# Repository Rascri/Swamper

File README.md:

# Swaby

## Descripción

**Swaby** es un proyecto investigativo orientado al desarrollo de un sistema portátil de monitoreo biomédico. El prototipo permite adquirir y visualizar en tiempo real información relacionada con la actividad cardíaca y el movimiento del usuario.

El sistema utiliza un **ESP32** como unidad principal de procesamiento, conectado a un sensor **AD8232** para la adquisición del electrocardiograma (ECG), un **DS18B20** para la medición de temperatura y un **MPU-6050** para el análisis de movimiento y postura.

Los datos obtenidos son procesados por el ESP32 y enviados mediante **Bluetooth** a una PC para su visualización y registro.

## Enfoque investigativo

El desarrollo de Swaby se planteó como un proyecto investigativo, además de la construcción de un prototipo funcional. Durante las pruebas se analizaron las condiciones necesarias para obtener una señal de ECG estable y las limitaciones del sistema.

Se comprobó que el ECG funciona correctamente cuando el usuario se encuentra en reposo, pero presenta importantes perturbaciones durante el movimiento. El principal problema identificado fue el ruido generado por la actividad y el movimiento muscular, que se superpone a la señal cardíaca y genera artefactos que dificultan su correcta interpretación.

A pesar del filtrado incorporado en el AD8232, filtrado por software y los recursos disponibles para el proyecto no fue posible eliminar estas interferencias de manera suficiente como para obtener una señal de ECG confiable durante el movimiento. Por este motivo, el monitoreo cardíaco se consideró funcional bajo condiciones de reposo, pero limitado durante la actividad física.

También se detectaron interferencias externas durante las primeras pruebas, relacionadas con la alimentación y la calidad de los electrodos. Estas fueron reducidas mediante el aislamiento de la fuente de alimentación utilizada en el laboratorio y el reemplazo de los electrodos por otros de mayor calidad.

## Software

El **ESP32** se encarga de adquirir los datos de los sensores y transmitirlos mediante Bluetooth.

Para la visualización y registro de los datos se desarrolló una aplicación en **Processing**, encargada de recibir la información enviada por el ESP32 y representarla de forma gráfica en tiempo real.

La aplicación permite visualizar principalmente:

* Señal de ECG y BPM en tiempo real.
* Datos de temperatura.
* Información proveniente del MPU-6050.

La comunicación entre el prototipo y la aplicación se realiza de forma inalámbrica mediante **Bluetooth**, permitiendo separar físicamente el sistema de adquisición de la interfaz de visualización.

## Estado del proyecto

El prototipo logró cumplir con el objetivo planteado, permitiendo la adquisición y visualización en tiempo real de las variables estudiadas.

El repositorio contiene el código, componentes, diagramas y documentación correspondiente al desarrollo de **Swaby**.

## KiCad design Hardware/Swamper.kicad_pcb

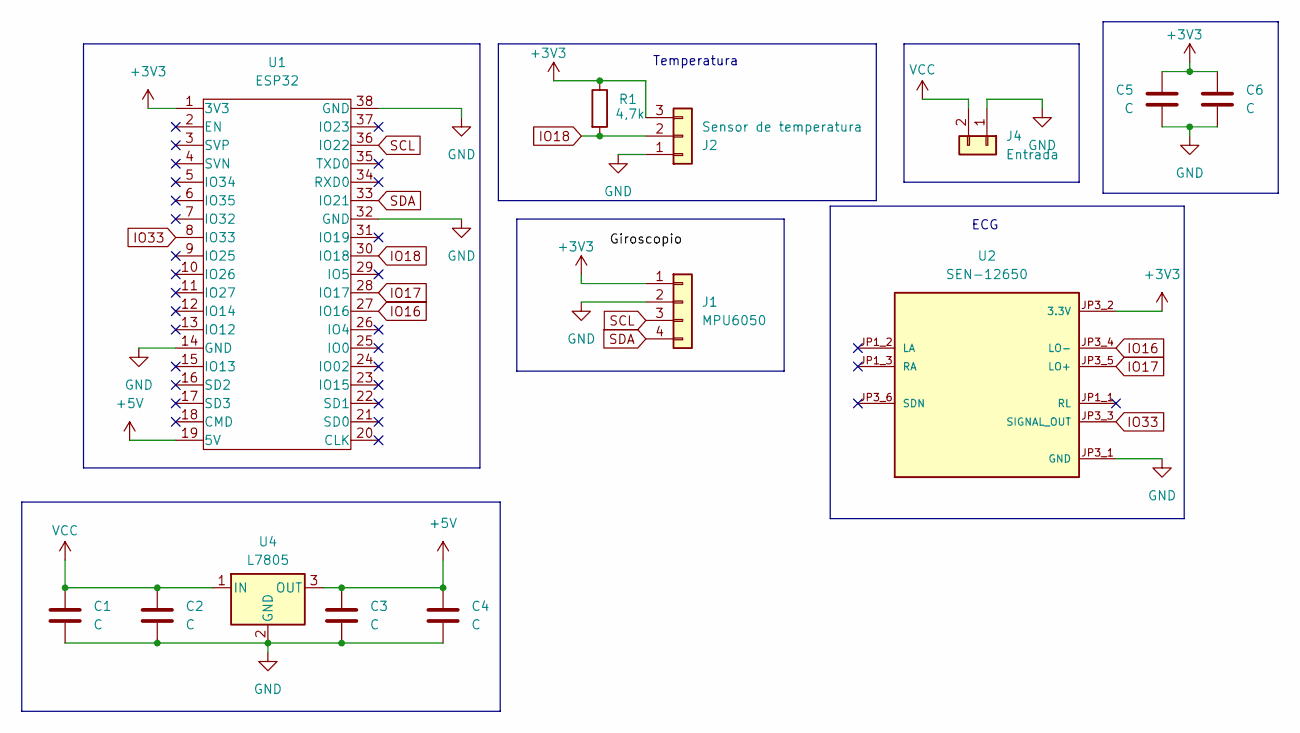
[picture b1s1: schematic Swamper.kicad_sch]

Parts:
C1, C4, C6: C; C_Elec_5x5.8
C2, C3, C5: C; C_0805_2012Metric_Pad1.18x1.45mm_HandSolder
J1: MPU6050; MPU6050_Module
J2: Sensor de temperatura; JST-3V
J4: Entrada; AMASS_XT30UPB-F_1x02_P5.0mm_Vertical
R1: 4,7k; R_0805
U1: ESP32; ESP32S
U2: SEN-12650; MODULE_SEN-12650; PARTREV V10
U4: L7805; TO-263-3_TabPin2

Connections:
+3V3: C5.1, C6.1, J1.1, J2.3, R1.1, U1.1 (3V3), U2.JP3_2 (3.3V)
+5V: C3.1, C4.1, U1.19 (5V), U4.3 (OUT)
GND: C1.2, C2.2, C3.2, C4.2, C5.2, C6.2, J1.2, J2.1, J4.1, U1.14 (GND), U1.32 (GND), U1.38 (GND), U2.JP3_1 (GND), U4.2 (GND); also elsewhere on the board
IO16: U1.27 (IO16), U2.JP3_4 (LO-)
IO17: U1.28 (IO17), U2.JP3_5 (LO+)
IO18: J2.2, R1.2, U1.30 (IO18)
IO33: U1.8 (IO33), U2.JP3_3 (SIGNAL_OUT)
SCL: J1.3, U1.36 (IO22)
SDA: J1.4, U1.33 (IO21)
VCC: C1.1, C2.1, J4.2, U4.1 (IN); also elsewhere on the board

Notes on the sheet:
ECG
Temperatura

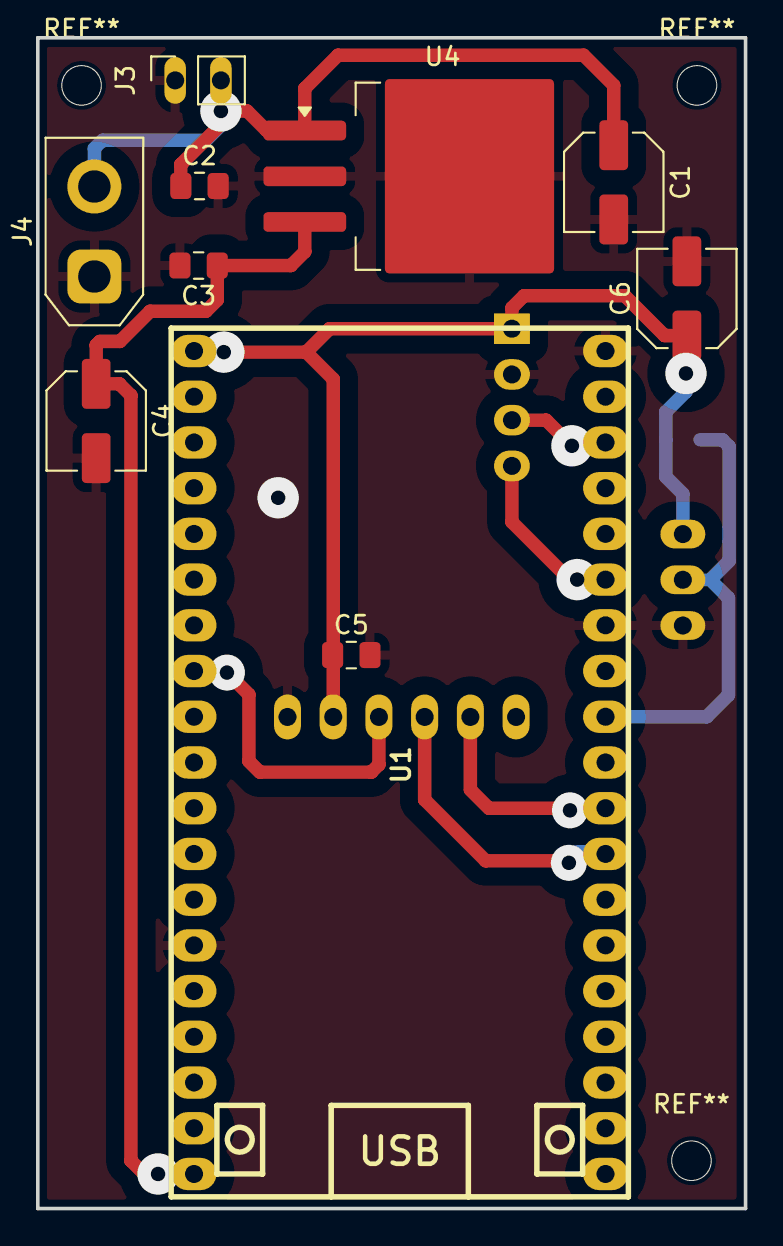
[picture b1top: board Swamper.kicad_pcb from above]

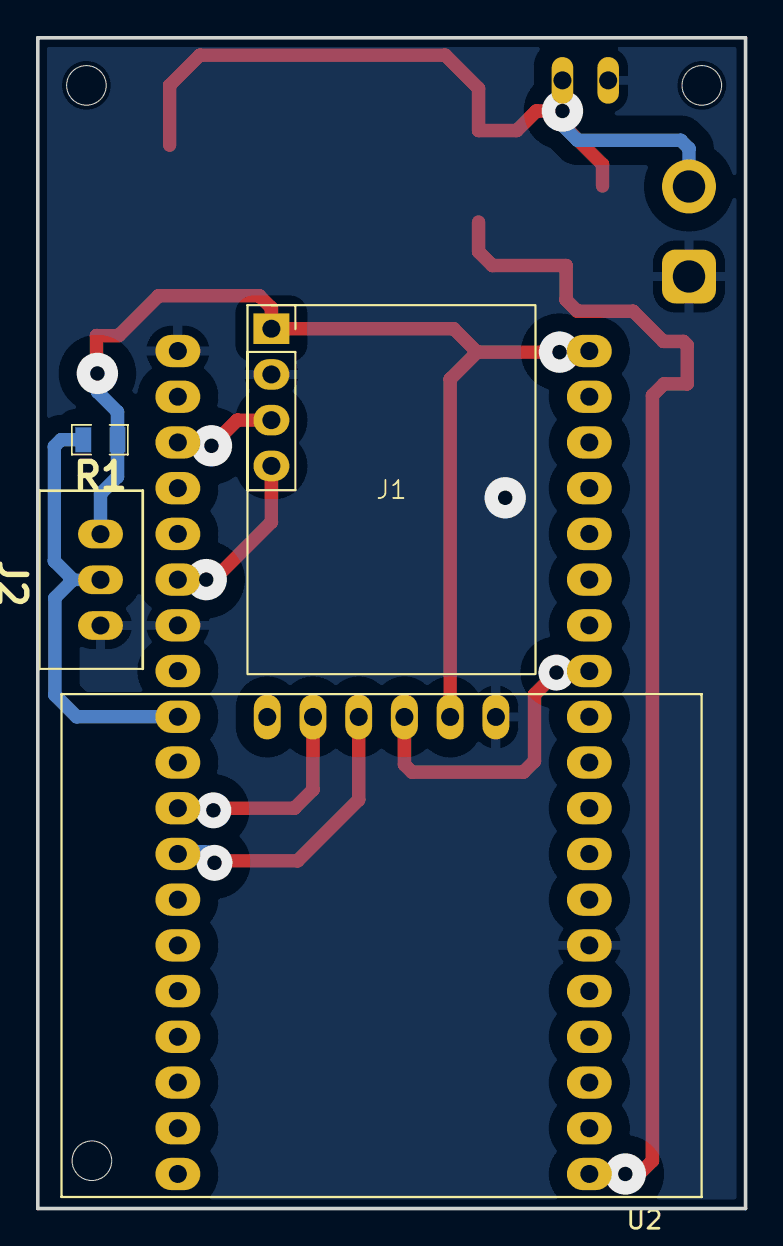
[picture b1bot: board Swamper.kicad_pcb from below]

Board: 2 copper layers, 39.3 x 65.0 mm, 14 parts (4 on the bottom side), 10 nets.

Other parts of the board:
J3: Entrada; PinSocket_1x02_P2.54mm_Vertical

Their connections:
GND: J3.1; also elsewhere on the board
VCC: J3.2; also elsewhere on the board

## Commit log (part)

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2026-04-17 Subo carpetas
2026-06-14 Actualizacion de repositorio
2026-06-15 Subo actualizaciones
